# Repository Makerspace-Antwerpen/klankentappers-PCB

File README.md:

# klankentappers-PCB

## The goal
The goal of this project was to create a cheap mic pcb that can be used to measure soundlevels with inexpensive hardware. 
The PCB's shape is dictated by the housing. 

## The components
### INFINEON M69d120
This is your run of the mill PDM microphone. It was picked because of it's flat frequency response.
### ADAU 7002
This is a PDM to I2S converter chip. It converts the PDM signal of the microphone to a I2S signal that is usable by for example a raspberry pi or a variety of microcontrollers.

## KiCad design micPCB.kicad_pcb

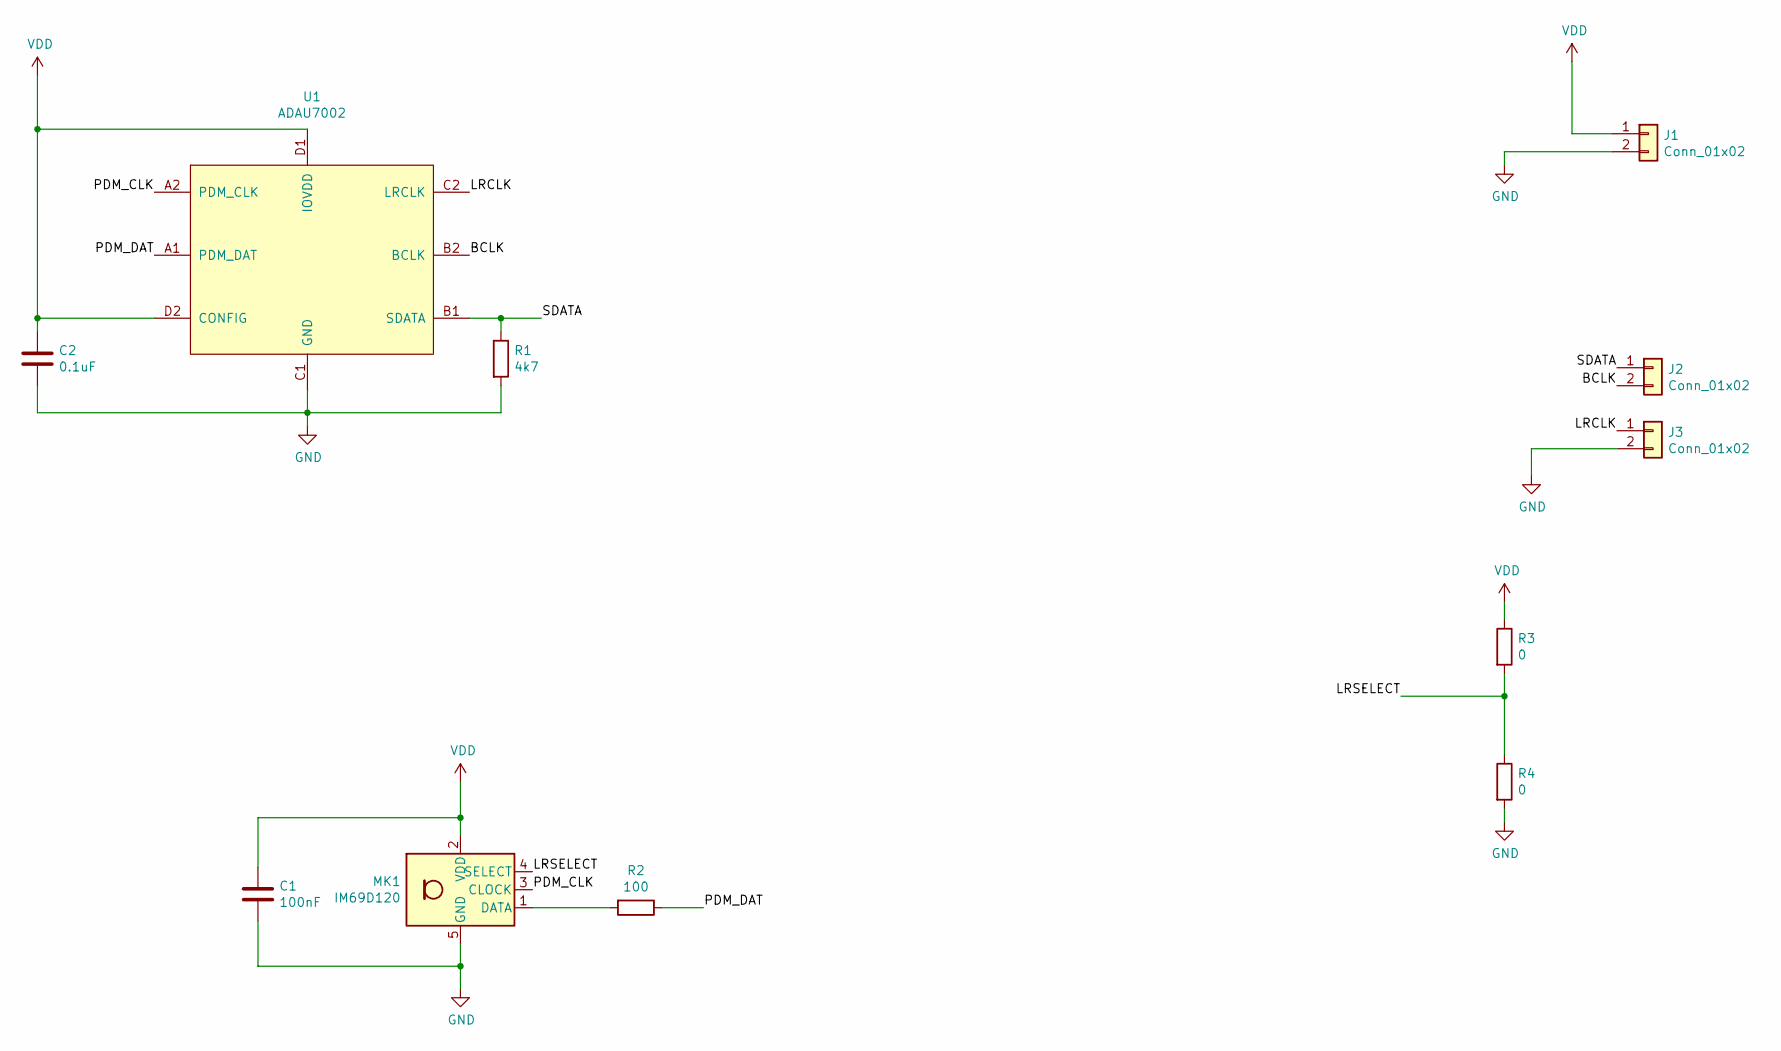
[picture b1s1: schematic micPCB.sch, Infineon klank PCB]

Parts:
C1: 100nF; C_0402_1005Metric; LCSC C1525
C2: 0.1uF; C_0402_1005Metric; LCSC C1525
J1, J2, J3: Conn_01x02; PinHeader_1x02_P2.54mm_Vertical_SMD_Pin1Right
MK1: IM69D120; Infineon_PG-LLGA-5-1
R1: 4k7; R_0402_1005Metric; LCSC C25900
R2: 100; R_0402_1005Metric; LCSC C25076
R3, R4: 0; R_0402_1005Metric
U1: ADAU7002; BGA-8_2x4_0.8x1.6mm

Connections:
/BCLK: J2.2, U1.B2 (BCLK)
/LRCLK: J3.1, U1.C2 (LRCLK)
/LRSELECT: MK1.4 (SELECT), R3.2, R4.1
/PDM_CLK: MK1.3 (CLOCK), U1.A2 (PDM_CLK)
/PDM_DAT: R2.1, U1.A1 (PDM_DAT)
/SDATA: J2.1, R1.1, U1.B1 (SDATA)
GND: C1.2, C2.2, J1.2, J3.2, MK1.5 (GND), R1.2, R4.2, U1.C1 (GND)
unnamed: MK1.1 (DATA), R2.2
VDD: C1.1, C2.1, J1.1, MK1.2 (VDD), R3.1, U1.D1 (IOVDD), U1.D2 (CONFIG)

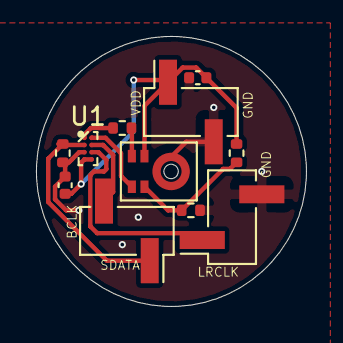
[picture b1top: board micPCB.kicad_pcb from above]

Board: 2 copper layers, 15.0 x 15.0 mm, 11 parts (0 on the bottom side), 9 nets.

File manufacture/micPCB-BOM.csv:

"Ref","Value","Footprint","Datasheet","Manufacturer","Vendor"
"C1","100nF","Capacitor_SMD:C_0402_1005Metric","~","",""
"C2","0.1uF","Capacitor_SMD:C_0402_1005Metric","~","",""
"J1","Conn_01x02","Connector_PinHeader_2.54mm:PinHeader_1x02_P2.54mm_Vertical","~","",""
"J2","Conn_01x03","Connector_PinHeader_2.54mm:PinHeader_1x03_P2.54mm_Vertical","~","",""
"J3","Conn_01x02","Connector_PinHeader_2.54mm:PinHeader_1x02_P2.54mm_Vertical","~","",""
"MK1","IM69D120","Sensor_Audio:Infineon_PG-LLGA-5-1","https://www.infineon.com/dgdl/Infineon-IM69D120-DS-v01_00-EN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","",""
"R1","4k7","Resistor_SMD:R_0402_1005Metric","~","",""
"R2","100","Resistor_SMD:R_0402_1005Metric","~","",""
"R3","0","Resistor_SMD:R_0402_1005Metric","~","",""
"R4","0","Resistor_SMD:R_0402_1005Metric","~","",""
"U1","ADAU7002","custom:BGA-8_2x4_0.8x1.6mm","","",""

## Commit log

2021-10-01 opened up space around via
